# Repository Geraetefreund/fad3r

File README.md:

# fad3r

v0.3 / 2025-05-15

Add: support for curves. So far lin, log, exp.
change: eeprom setup.

for example: ```F0 7D 43 <preset> <cc1> <cc2> <cc3> <ch1> <ch2> <ch3> <cv1> <cv2> <cv3> F7```

| Index | Byte      | Description            |
| ----- | --------- | ---------------------- |
| 0     | `0xF0`    | SysEx start            |
| 1     | `0x7D`    | Non-commercial ID      |
| 2     | `0x43`    | Dump command           |
| 3     | `Preset`  | Preset index           |
| 4–6   | `CC1–CC3` | Control change numbers |
| 7–9   | `CH1–CH3` | MIDI channels          |
| 10–12 | `CV1–CV3` | Curve values           |
| 13    | `0xF7`    | SysEx end              |

curves: 
0 linear
1 logarithmic
2 exponential

added curve per fader, so changed the eeprom layout a bit.

=================
v0.2 / 2025-05-14

Improved preset storage in EEPROM. Faders can now have indiviual MIDI channels.  

Load preset:  
``` F0 7D 40 <preset> F7```

Store current CC/Channel values to preset:  
```F0 7D 41 <preset> F7```

Set CCs and Channels for preset (remember dec to hex!):  
```F0 7D 42 <preset> <cc1> <cc2> <cc3> <ch1> <ch2> <ch3> F7```  

Dump preset: ``` F0 7D 43 <preset> F7```  

Returns: ```F0 7D 43 <preset> <cc1> <cc2> <cc3> <ch1> <ch2> <ch3> F7```

Get current preset: 
``` F0 7D 44 00 F7``` returns ```F0 7D 44 <current preset> F7```

=================
v0.1 / 2020-02-12

Firmware for Teensy LC (legacy) controlling three faders via USB Midi  

https://www.pjrc.com/store/teensylc.html  
https://www.pjrc.com/teensy/td_midi.html  

``` F0 7D <cc1> <cc2> <cc3> F7```
remember to convert from dec to hex!

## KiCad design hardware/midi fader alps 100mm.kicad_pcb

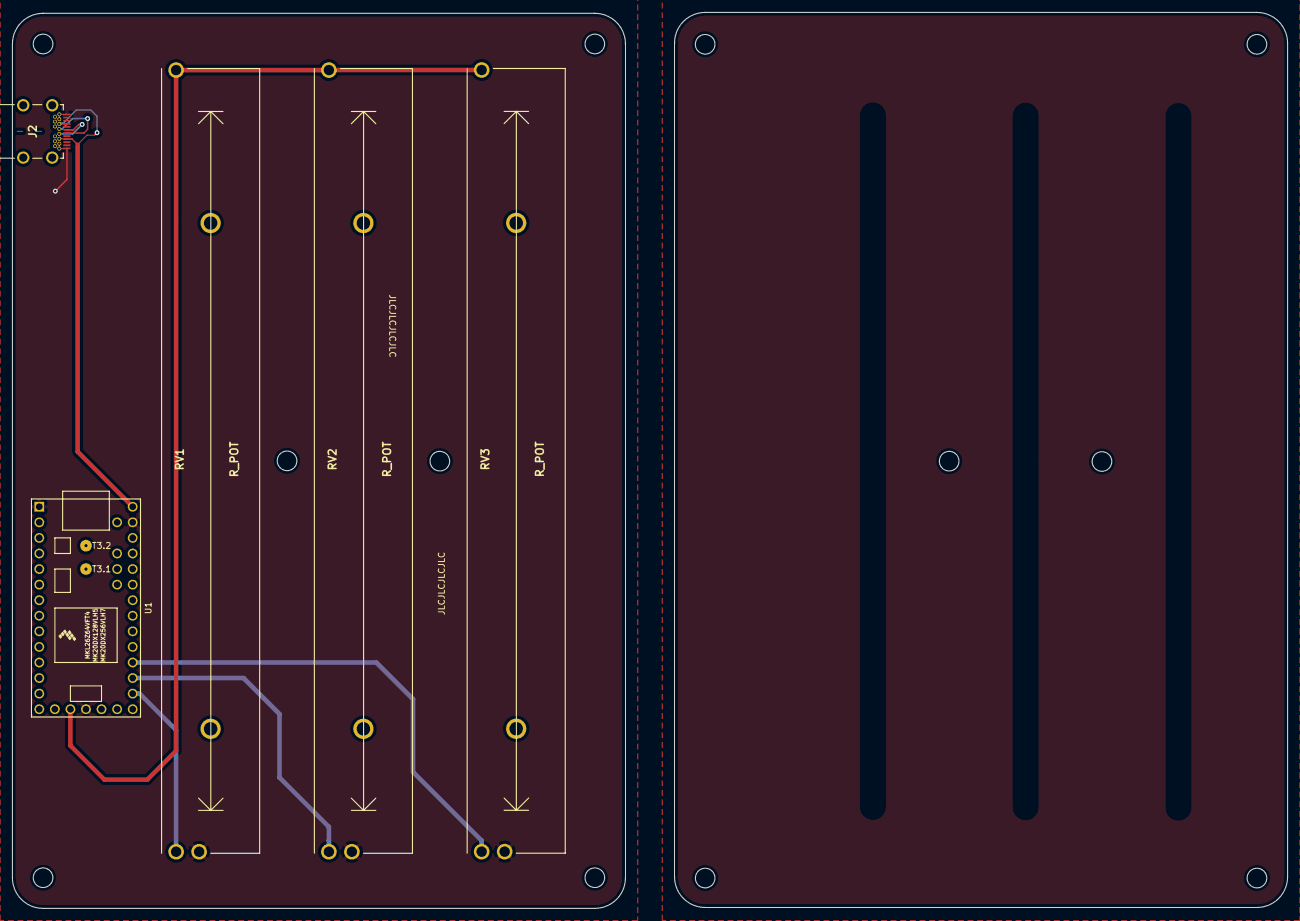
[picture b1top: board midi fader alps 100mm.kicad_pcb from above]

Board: 2 copper layers, 100.0 x 146.0 mm, 5 parts (0 on the bottom side), 8 nets.

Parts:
J2: 632723300011
RV1, RV2, RV3: R_POT; Alps_RSA0N111900Q
U1: Teensy-LC; Teensy30_31_32_LC

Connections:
+3V3: RV1.3, RV2.3, RV3.3, U1.16
+5V: J2.A4, J2.A9, J2.B4, J2.B9, U1.33
/ADC_1: RV1.2, U1.21
/ADC_2: RV2.2, U1.22
/ADC_3: RV3.2, U1.23
/D+: J2.A6, J2.B6
/D-: J2.A7, J2.B7
GND: J2.1, J2.2, J2.A1, J2.A12, J2.B1, J2.B12, RV1.1, RV2.1, RV3.1, U1.1, U1.17, U1.32

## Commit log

2025-05-14 version 0.1 working with eeprom and sysex
2025-05-14 improved sysex handling, added presets and separate channgels per fader
2025-05-14 fixed bug.
2025-05-15 add sysex for get current preset
2025-05-15 fix: after sysex call, no need to wiggle a fader
2025-05-15 Update README.md
    typo
2025-05-15 v0.3 add curves, changed eeprom layout
